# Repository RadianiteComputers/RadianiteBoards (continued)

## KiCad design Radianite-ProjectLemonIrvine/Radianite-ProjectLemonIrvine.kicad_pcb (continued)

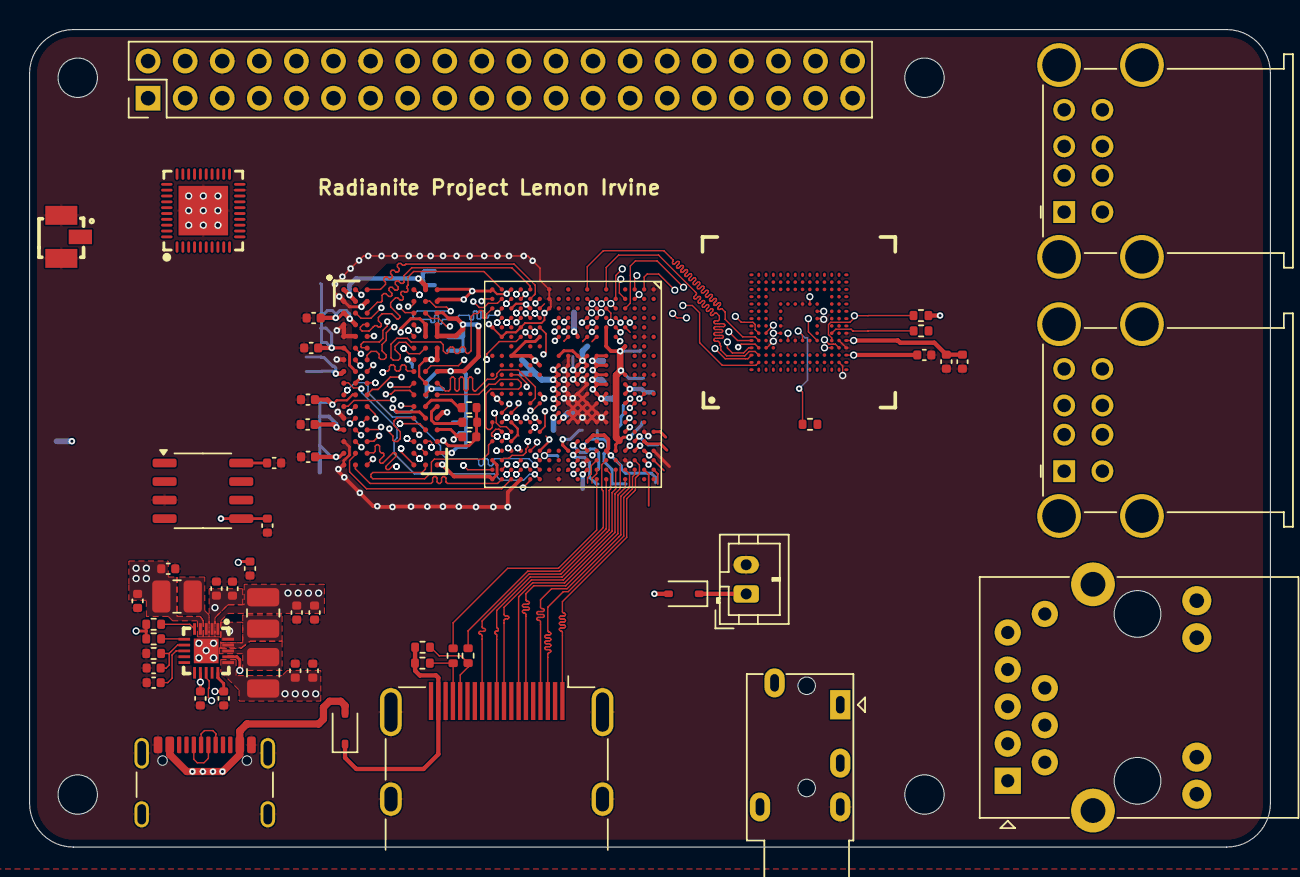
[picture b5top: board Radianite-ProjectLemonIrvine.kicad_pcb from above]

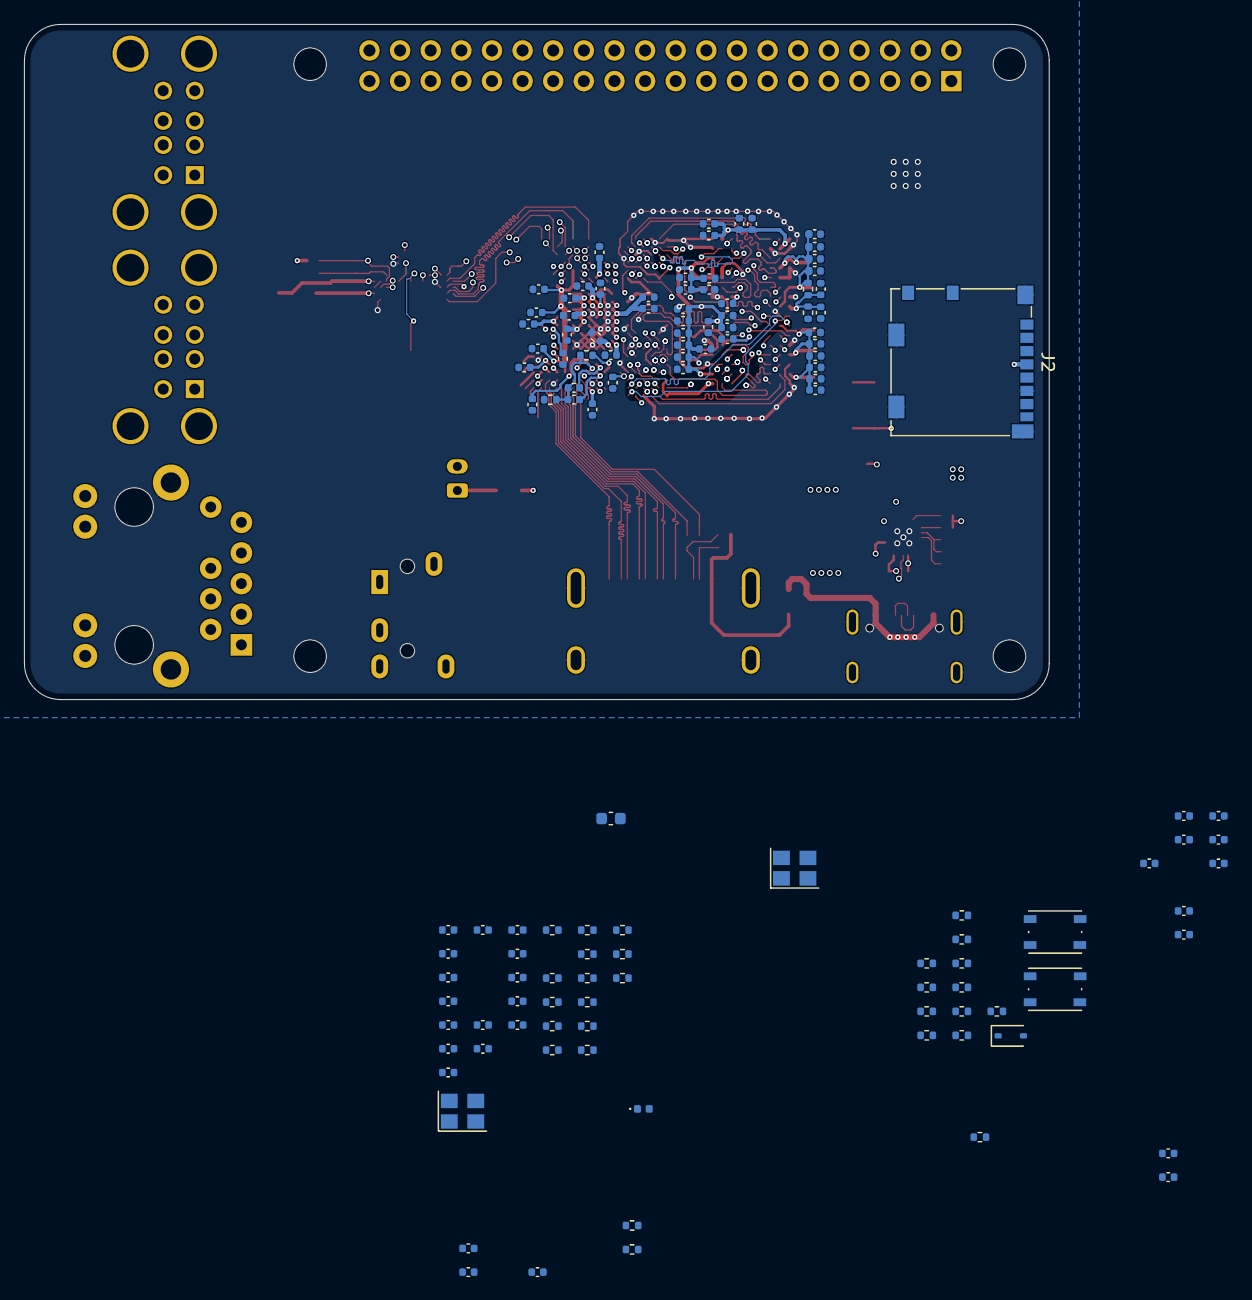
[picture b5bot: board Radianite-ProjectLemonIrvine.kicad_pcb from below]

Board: 6 copper layers, 85.0 x 56.0 mm, 181 parts (121 on the bottom side), 211 nets.

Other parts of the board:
C34#2, C35#2, C36#2, C55#2: 100n; C_0402_1005Metric

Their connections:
GND: C34#2.2, C35#2.2, C36#2.2, C55#2.2; also elsewhere on the board
VRAM: C34#2.1, C35#2.1, C36#2.1, C55#2.1; also elsewhere on the board

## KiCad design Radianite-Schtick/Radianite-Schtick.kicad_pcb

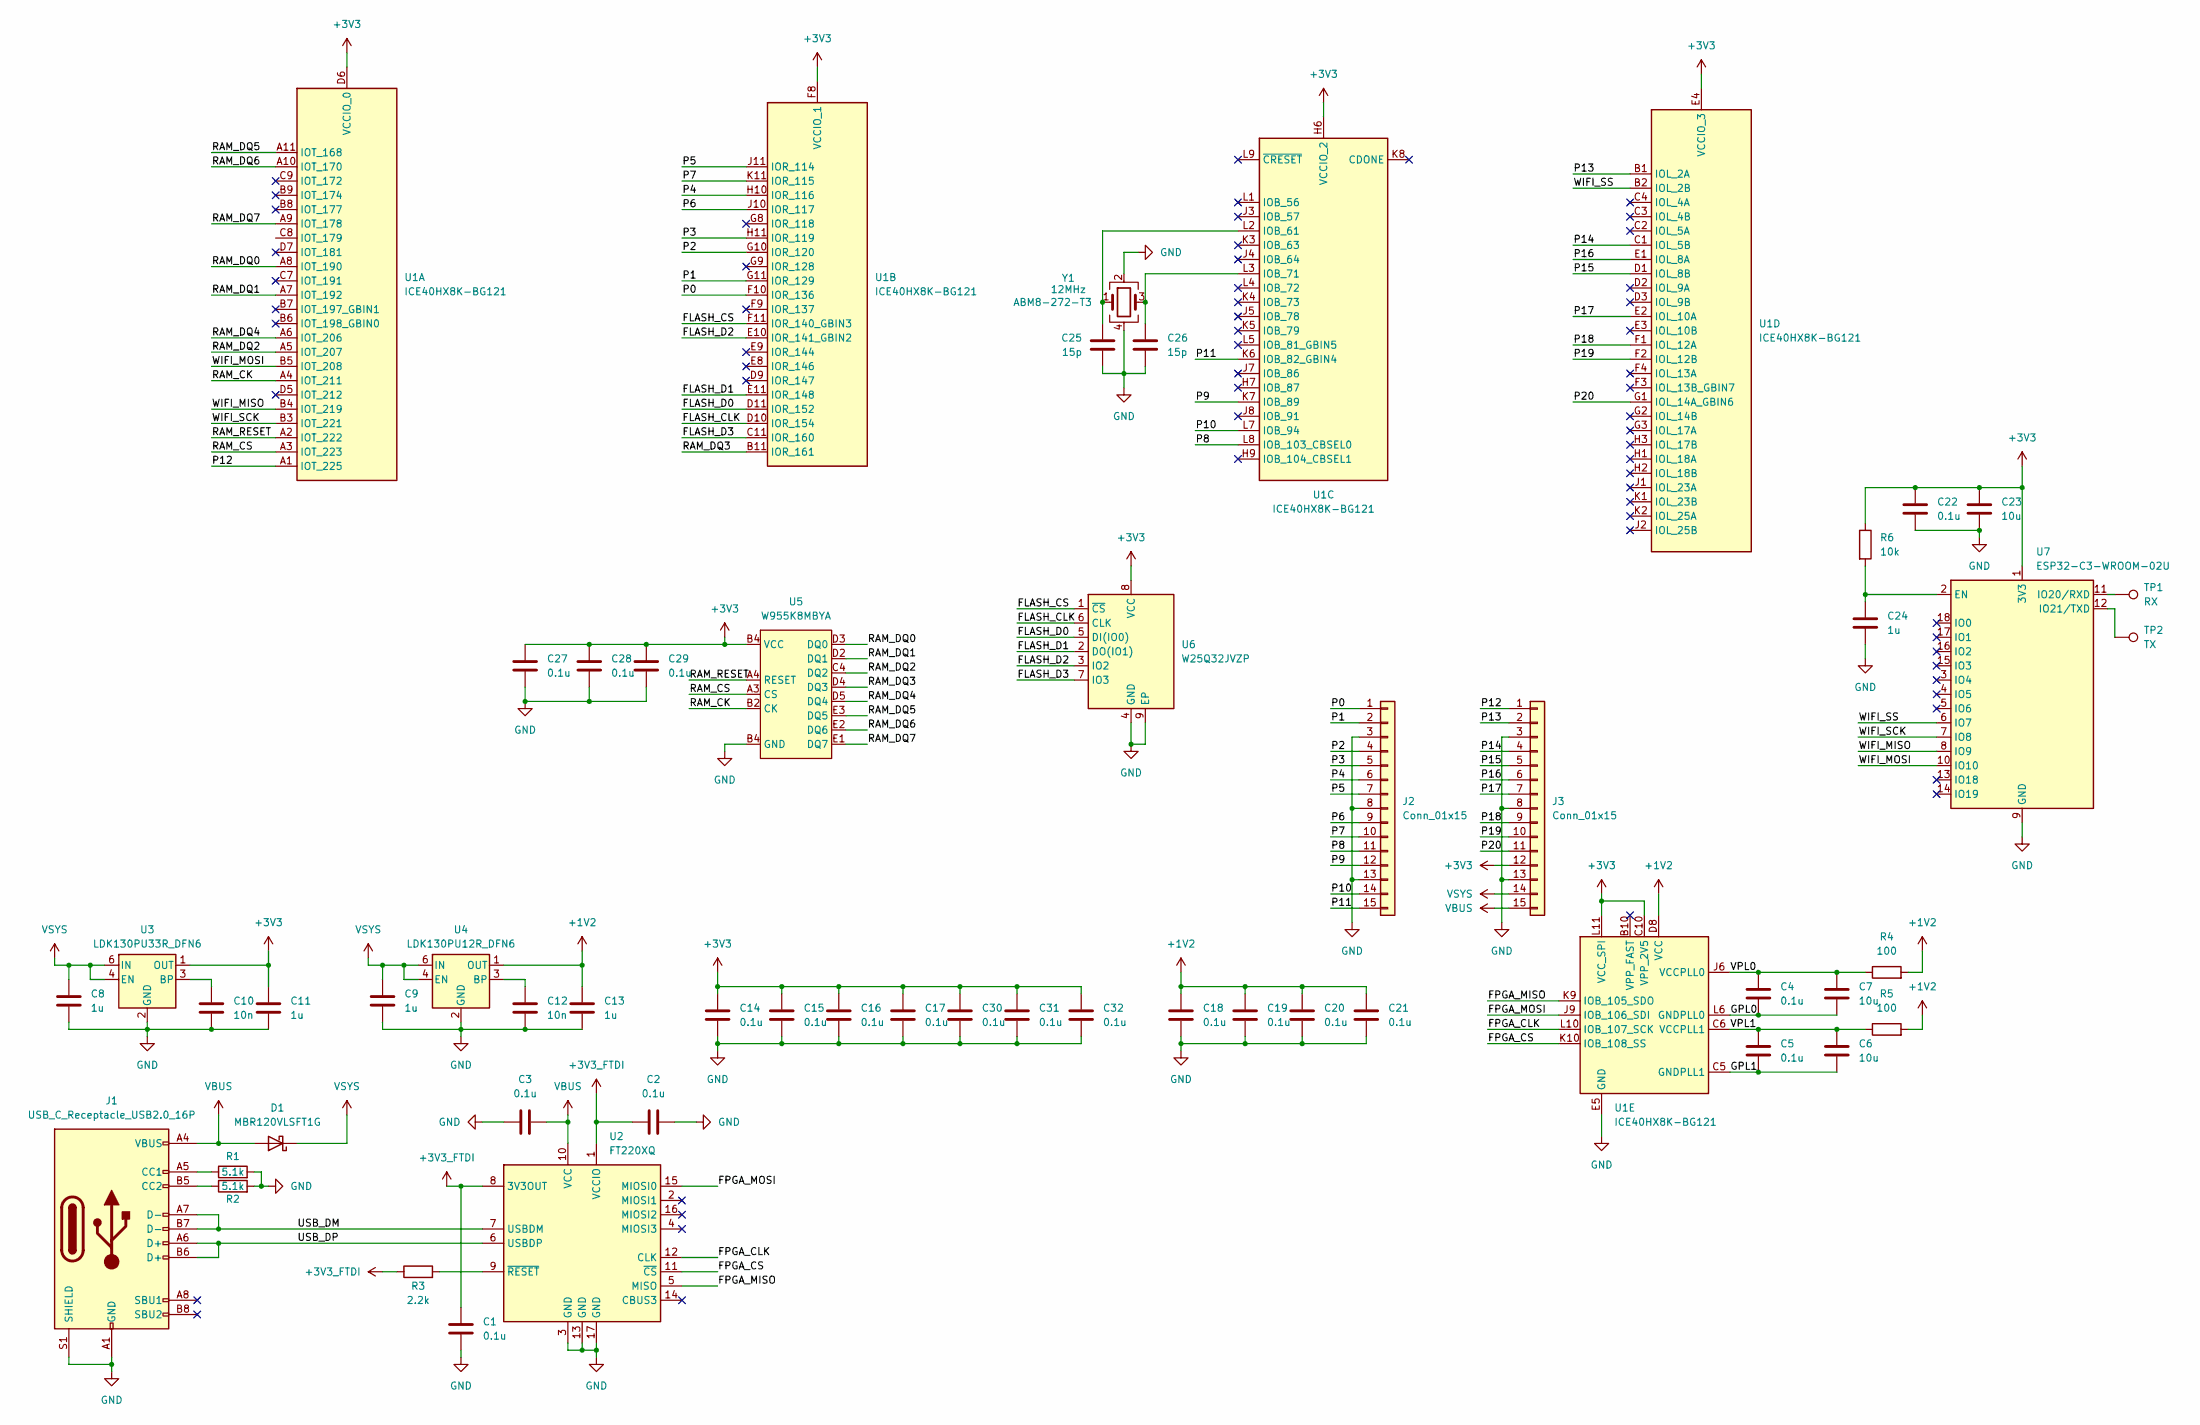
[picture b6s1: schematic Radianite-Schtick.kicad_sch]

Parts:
C1, C2, C3, C4, C5, C14, C15, C16, C17, C18, C19, C20, C21, C22, C27, C28, C29, C30, C31, C32: 0.1u; C_0402_1005Metric
C6, C7, C23: 10u; C_0402_1005Metric
C8, C9, C11, C13, C24: 1u; C_0402_1005Metric
C10, C12: 10n; C_0402_1005Metric
C25, C26: 15p; C_0402_1005Metric
D1: MBR120VLSFT1G; D_SOD-123F
J1: USB_C_Receptacle_USB2.0_16P; USB_C_Receptacle_GCT_USB4105-xx-A_16P_TopMnt_Horizontal
J2, J3: Conn_01x15; PinHeader_1x15_P2.54mm_Vertical
R1, R2: 5.1k; R_0402_1005Metric
R3: 2.2k; R_0402_1005Metric
R4, R5: 100; R_0402_1005Metric
R6: 10k; R_0402_1005Metric
TP1: RX; TestPoint_Pad_D1.0mm
TP2: TX; TestPoint_Pad_D1.0mm
U1: ICE40HX8K-BG121; BGA-121_9.0x9.0mm_Layout11x11_P0.8mm_Ball0.4mm_Pad0.35mm_NS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
U2: FT220XQ; QFN-16-1EP_4x4mm_P0.65mm_EP2.1x2.1mm
U3: LDK130PU33R_DFN6; DFN-6_1.3x1.2mm_P0.4mm
U4: LDK130PU12R_DFN6; DFN-6_1.3x1.2mm_P0.4mm
U5: W955K8MBYA
U6: W25Q32JVZP; Winbond_USON-8-1EP_3x2mm_P0.5mm_EP0.2x1.6mm
U7: ESP32-C3-WROOM-02U
Y1: 12MHz; Crystal_SMD_3225-4Pin_3.2x2.5mm

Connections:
+1V2: C13.1, C18.1, C19.1, C20.1, C21.1, R4.2, R5.2, U1.D4 (VCC), U1.D8 (VCC), U1.H4 (VCC), U1.H8 (VCC), U4.1 (OUT)
+3V3_FTDI: C1.1, C2.1, R3.1, U2.1 (VCCIO), U2.8 (3V3OUT)
/FLASH_CLK: U1.D10 (IOR_154), U6.6 (CLK)
/FLASH_CS: U1.F11 (IOR_140_GBIN3), U6.1 (~CS)
/FLASH_D0: U1.D11 (IOR_152), U6.5 (DI(IO0))
/FLASH_D1: U1.E11 (IOR_148), U6.2 (DO(IO1))
/FLASH_D2: U1.E10 (IOR_141_GBIN2), U6.3 (IO2)
/FLASH_D3: U1.C11 (IOR_160), U6.7 (IO3)
/FPGA_CLK: U1.L10 (IOB_107_SCK), U2.12 (CLK)
/FPGA_CS: U1.K10 (IOB_108_SS), U2.11 (~CS)
/FPGA_MISO: U1.K9 (IOB_105_SDO), U2.5 (MISO)
/FPGA_MOSI: U1.J9 (IOB_106_SDI), U2.15 (MIOSI0)
/GPL0: C4.2, C7.2, U1.L6 (GNDPLL0)
/GPL1: C5.2, C6.2, U1.C5 (GNDPLL1)
/P0: J2.1, U1.F10 (IOR_136)
/P1: J2.2, U1.G11 (IOR_129)
/P2: J2.4, U1.G10 (IOR_120)
/P3: J2.5, U1.H11 (IOR_119)
/P4: J2.6, U1.H10 (IOR_116)
/P5: J2.7, U1.J11 (IOR_114)
/P6: J2.9, U1.J10 (IOR_117)
/P7: J2.10, U1.K11 (IOR_115)
/P8: J2.11, U1.L8 (IOB_103_CBSEL0)
/P9: J2.12, U1.K7 (IOB_89)
/P10: J2.14, U1.L7 (IOB_94)
/P11: J2.15, U1.K6 (IOB_82_GBIN4)
/P12: J3.1, U1.A1 (IOT_225)
/P13: J3.2, U1.B1 (IOL_2A)
/P14: J3.4, U1.C1 (IOL_5B)
/P15: J3.5, U1.D1 (IOL_8B)
/P16: J3.6, U1.E1 (IOL_8A)
/P17: J3.7, U1.E2 (IOL_10A)
/P18: J3.9, U1.F1 (IOL_12A)
/P19: J3.10, U1.F2 (IOL_12B)
/P20: J3.11, U1.G1 (IOL_14A_GBIN6)
/RAM_CK: U1.A4 (IOT_211), U5.B2 (CK)
/RAM_CS: U1.A3 (IOT_223), U5.A3 (CS)
/RAM_DQ0: U1.A8 (IOT_190), U5.D3 (DQ0)
/RAM_DQ1: U1.A7 (IOT_192), U5.D2 (DQ1)
/RAM_DQ2: U1.A5 (IOT_207), U5.C4 (DQ2)
/RAM_DQ3: U1.B11 (IOR_161), U5.D4 (DQ3)
/RAM_DQ4: U1.A6 (IOT_206), U5.D5 (DQ4)
/RAM_DQ5: U1.A11 (IOT_168), U5.E3 (DQ5)
/RAM_DQ6: U1.A10 (IOT_170), U5.E2 (DQ6)
/RAM_DQ7: U1.A9 (IOT_178), U5.E1 (DQ7)
/RAM_RESET: U1.A2 (IOT_222), U5.A4 (RESET)
/USB_DM: J1.A7 (D-), J1.B7 (D-), U2.7 (USBDM)
/USB_DP: J1.A6 (D+), J1.B6 (D+), U2.6 (USBDP)
/VPL0: C4.1, C7.1, R4.1, U1.J6 (VCCPLL0)
/VPL1: C5.1, C6.1, R5.1, U1.C6 (VCCPLL1)
/WIFI_MISO: U1.B4 (IOT_219), U7.8 (IO9)
/WIFI_MOSI: U1.B5 (IOT_208), U7.10 (IO10)
/WIFI_SCK: U1.B3 (IOT_221), U7.7 (IO8)
/WIFI_SS: U1.B2 (IOL_2B), U7.6 (IO7)
unnamed: J1.A5 (CC1), R1.1
unnamed: J1.B5 (CC2), R2.1
unnamed: C25.1, U1.L2 (IOB_61), Y1.1
unnamed: C26.1, U1.L3 (IOB_71), Y1.3
unnamed: R3.2, U2.9 (~RESET)
unnamed: C10.1, U3.3 (BP)
unnamed: C12.1, U4.3 (BP)
unnamed: C24.1, R6.2, U7.2 (EN)
unnamed: TP1.1, U7.11 (IO20/RXD)
unnamed: TP2.1, U7.12 (IO21/TXD)
VBUS: C3.2, D1.2 (A), J1.A4 (VBUS), J1.A9 (VBUS), J1.B4 (VBUS), J1.B9 (VBUS), J3.15, U2.10 (VCC)
VSYS: C8.1, C9.1, D1.1 (K), J3.14, U3.4 (EN), U3.6 (IN), U4.4 (EN), U4.6 (IN)

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
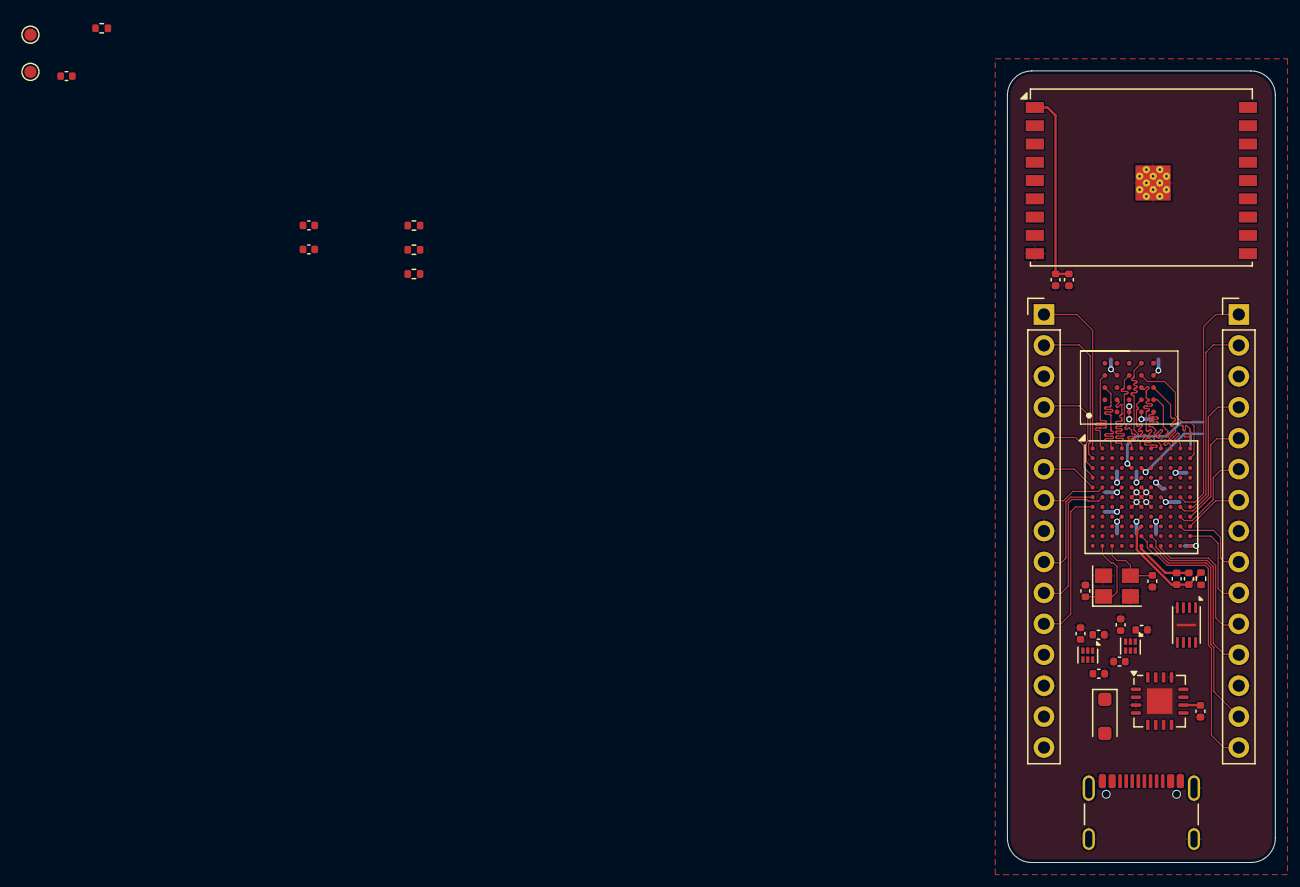
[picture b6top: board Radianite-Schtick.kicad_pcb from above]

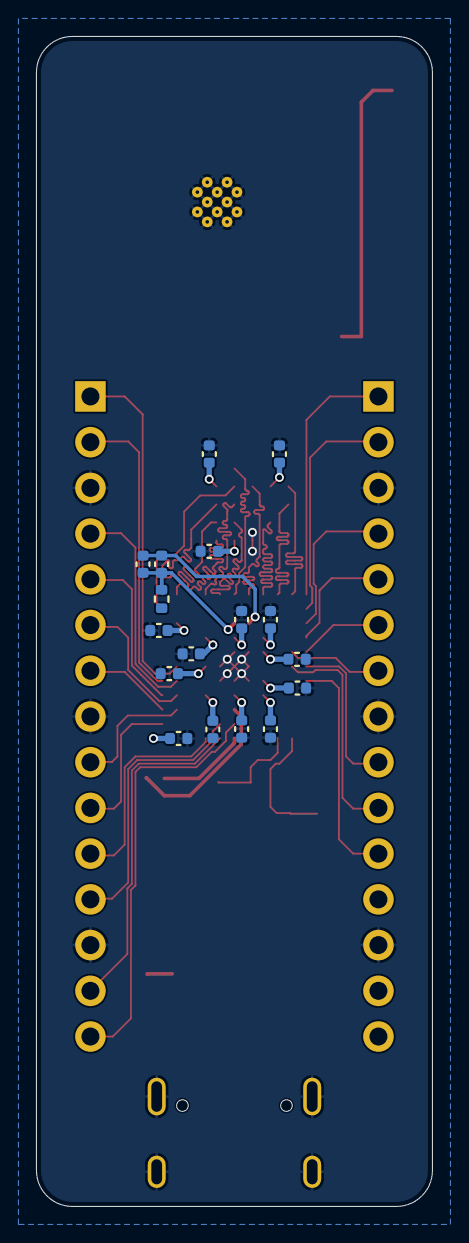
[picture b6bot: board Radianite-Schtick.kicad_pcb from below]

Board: 4 copper layers, 22.0 x 65.0 mm, 52 parts (17 on the bottom side), 68 nets.

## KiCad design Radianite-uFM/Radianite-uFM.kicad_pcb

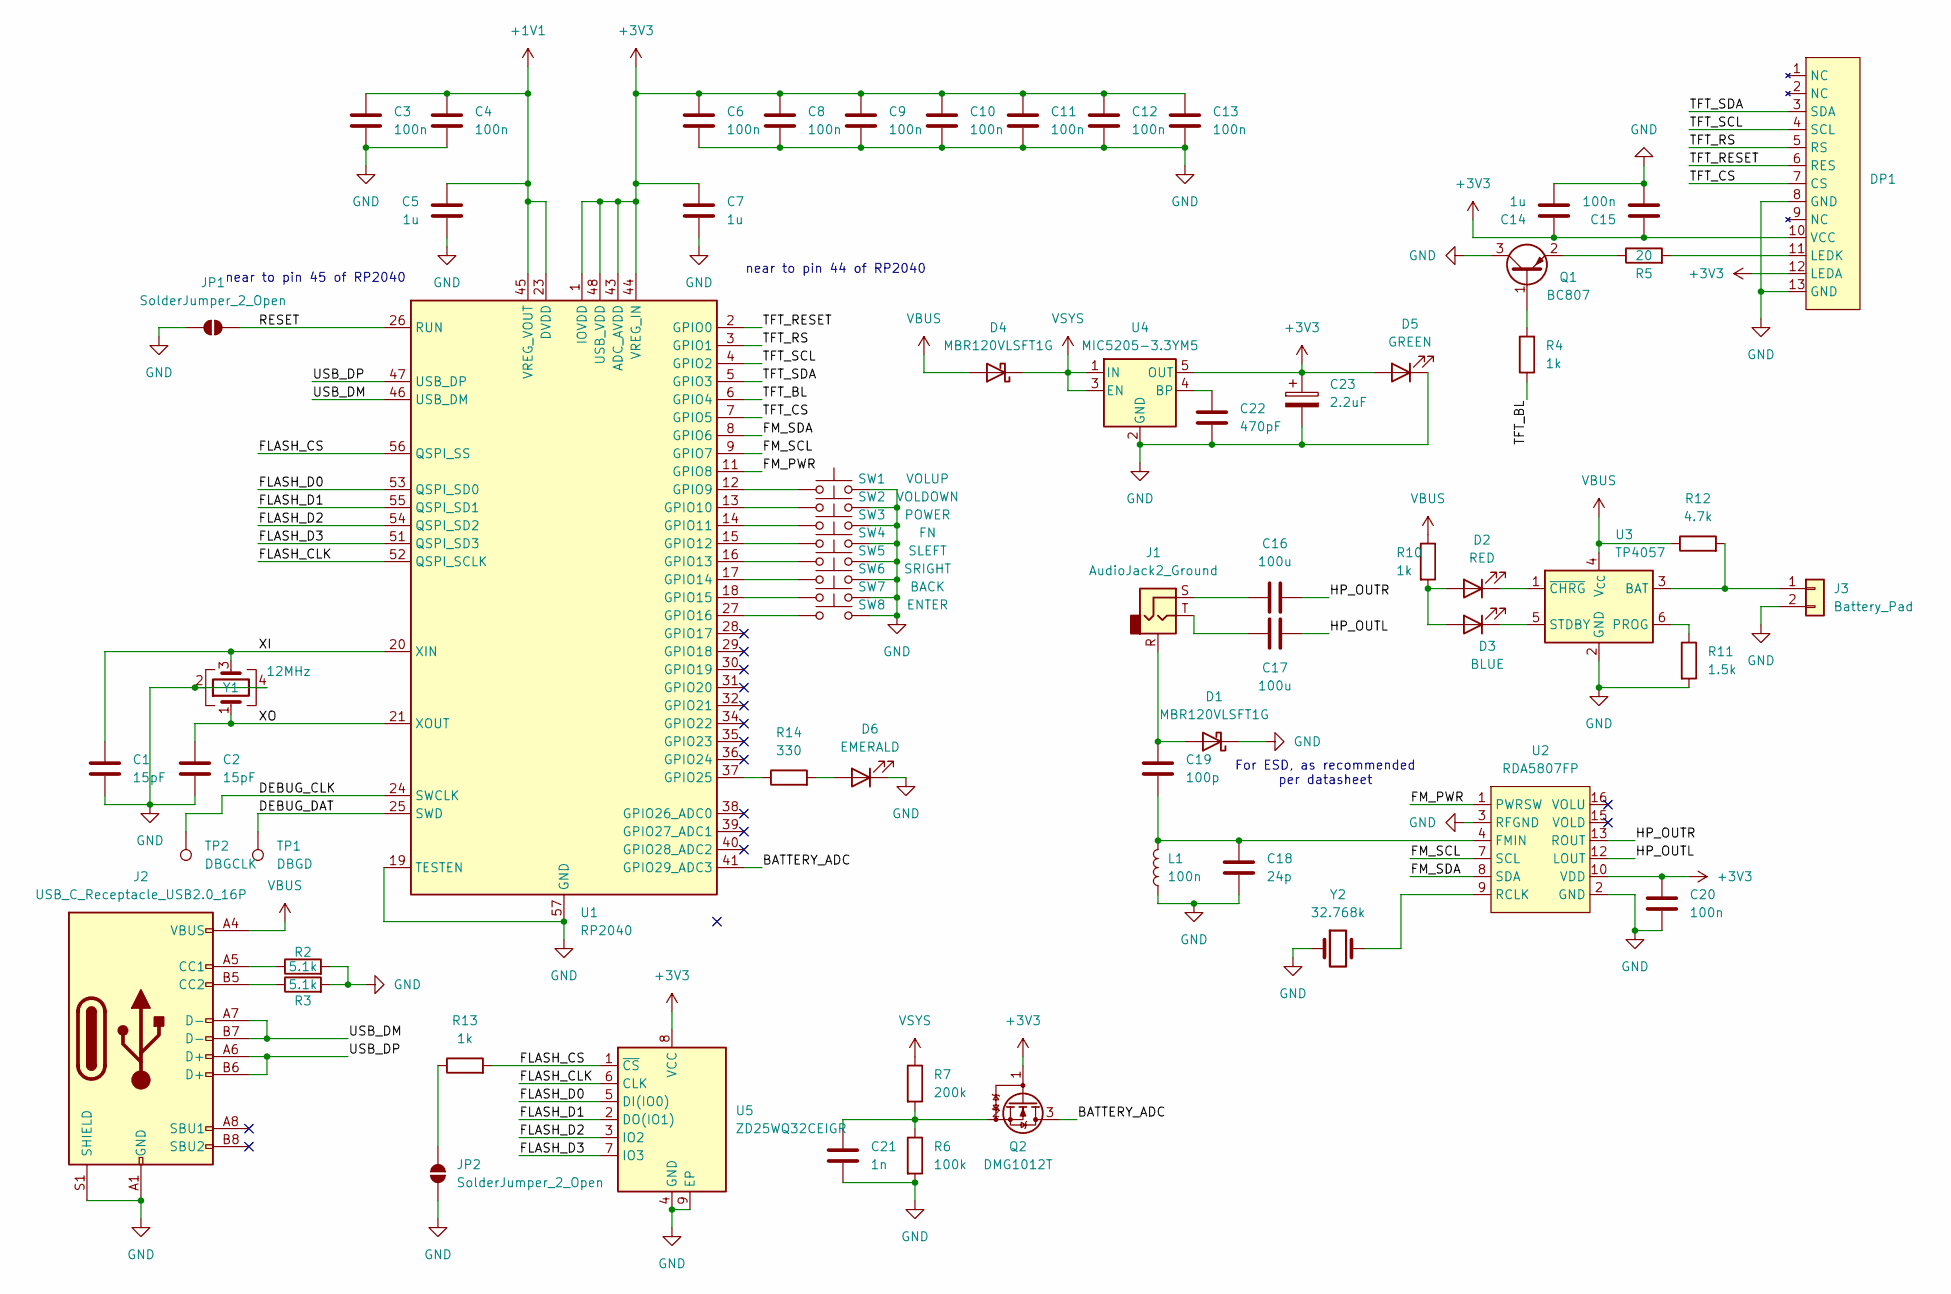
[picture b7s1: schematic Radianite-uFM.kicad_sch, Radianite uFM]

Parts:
C1, C2: 15pF; C_0402_1005Metric
C3, C4, C6, C8, C9, C10, C11, C12, C13, C15: 100n; C_0402_1005Metric
C5, C7, C14: 1u; C_0402_1005Metric
C16, C17: 100u; C_0603_1608Metric
C18: 24p; C_0603_1608Metric
C19: 100p; C_0603_1608Metric
C20: 100n; C_0603_1608Metric
C21: 1n; C_0402_1005Metric
C22: 470pF; C_0402_1005Metric
C23: 2.2uF; CP_EIA-1608-08_AVX-J
D1, D4: MBR120VLSFT1G; D_SOD-123F
D2: RED; LED_0402_1005Metric
D3: BLUE; LED_0402_1005Metric
D5: GREEN; LED_0402_1005Metric
D6: EMERALD; LED_0402_1005Metric
DP1: N114-2413THBIG01-H13
J1: AudioJack2_Ground; Jack_3.5mm_Lumberg_1503_07_Horizontal
J2: USB_C_Receptacle_USB2.0_16P; USB_C_Receptacle_GCT_USB4105-xx-A_16P_TopMnt_Horizontal
J3: Battery_Pad; SolderWire-0.1sqmm_1x02_P3.6mm_D0.4mm_OD1mm
JP1, JP2: SolderJumper_2_Open; SolderJumper-2_P1.3mm_Open_Pad1.0x1.5mm
L1: 100n; L_0603_1608Metric
Q1: BC807; SOT-23
Q2: DMG1012T; SOT-523
R2, R3: 5.1k; R_0402_1005Metric
R4, R10, R13: 1k; R_0402_1005Metric
R5: 20; R_0402_1005Metric
R6: 100k; R_0402_1005Metric
R7: 200k; R_0402_1005Metric
R11: 1.5k; R_0402_1005Metric
R12: 4.7k; R_0402_1005Metric
R14: 330; R_0402_1005Metric
SW1: VOLUP; SW_Push_1P1T-MP_NO_Horizontal_Alps_SKRTLAE010
SW2: VOLDOWN; SW_Push_1P1T-MP_NO_Horizontal_Alps_SKRTLAE010
SW3: POWER; SW_Push_1P1T-MP_NO_Horizontal_Alps_SKRTLAE010
SW4: FN; SW_Push_1P1T-MP_NO_Horizontal_Alps_SKRTLAE010
SW5: SLEFT; SW_Push_1P1T_NO_Vertical_Wuerth_434133025816
SW6: SRIGHT; SW_Push_1P1T_NO_Vertical_Wuerth_434133025816
SW7: BACK; SW_Push_1P1T_NO_Vertical_Wuerth_434133025816
SW8: ENTER; SW_Push_1P1T_NO_Vertical_Wuerth_434133025816
TP1: DBGD; TestPoint_Pad_D1.0mm
TP2: DBGCLK; TestPoint_Pad_D1.0mm
U1: RP2040; QFN-56-1EP_7x7mm_P0.4mm_EP3.2x3.2mm
U2: RDA5807FP; SOP-16_3.9x9.9mm_P1.27mm
U3: TP4057; TSOT-23-6
U4: MIC5205-3.3YM5; SOT-23-5
U5: ZD25WQ32CEIGR; Winbond_USON-8-1EP_3x2mm_P0.5mm_EP0.2x1.6mm
Y1: 12MHz; Crystal_SMD_2520-4Pin_2.5x2.0mm
Y2: 32.768k; Crystal_SMD_0603-2Pin_6.0x3.5mm

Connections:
+1V1: C3.1, C4.1, C5.1, U1.23 (DVDD), U1.45 (VREG_VOUT), U1.50 (DVDD)
+3V3: C6.1, C7.1, C8.1, C9.1, C10.1, C11.1, C12.1, C13.1, C14.1, C15.1, C20.1, C23.1, D5.2 (A), DP1.10 (VCC), DP1.12 (LEDA), Q2.1 (G), U1.1 (IOVDD), U1.10 (IOVDD), U1.22 (IOVDD), U1.33 (IOVDD), U1.42 (IOVDD), U1.43 (ADC_AVDD), U1.44 (VREG_IN), U1.48 (USB_VDD), U1.49 (IOVDD), U2.10 (VDD), U4.5 (OUT), U5.8 (VCC)
/BATTERY_ADC: Q2.3 (D), U1.41 (GPIO29_ADC3)
/DEBUG_CLK: TP2.1, U1.24 (SWCLK)
/DEBUG_DAT: TP1.1, U1.25 (SWD)
/FLASH_CLK: U1.52 (QSPI_SCLK), U5.6 (CLK)
/FLASH_CS: R13.2, U1.56 (QSPI_SS), U5.1 (~CS)
/FLASH_D0: U1.53 (QSPI_SD0), U5.5 (DI(IO0))
/FLASH_D1: U1.55 (QSPI_SD1), U5.2 (DO(IO1))
/FLASH_D2: U1.54 (QSPI_SD2), U5.3 (IO2)
/FLASH_D3: U1.51 (QSPI_SD3), U5.7 (IO3)
/FM_PWR: U1.11 (GPIO8), U2.1 (PWRSW)
/FM_SCL: U1.9 (GPIO7), U2.7 (SCL)
/FM_SDA: U1.8 (GPIO6), U2.8 (SDA)
/HP_OUTL: C17.2, U2.12 (LOUT)
/HP_OUTR: C16.2, U2.13 (ROUT)
/RESET: JP1.2 (B), U1.26 (RUN)
/TFT_BL: R4.1, U1.6 (GPIO4)
/TFT_CS: DP1.7 (CS), U1.7 (GPIO5)
/TFT_RESET: DP1.6 (RES), U1.2 (GPIO0)
/TFT_RS: DP1.5 (RS), U1.3 (GPIO1)
/TFT_SCL: DP1.4 (SCL), U1.4 (GPIO2)
/TFT_SDA: DP1.3 (SDA), U1.5 (GPIO3)
/USB_DM: J2.A7 (D-), J2.B7 (D-), U1.46 (USB_DM)
/USB_DP: J2.A6 (D+), J2.B6 (D+), U1.47 (USB_DP)
/XI: C1.1, U1.20 (XIN), Y1.3
/XO: C2.1, U1.21 (XOUT), Y1.1
GND: C1.2, C2.2, C3.2, C4.2, C5.2, C6.2, C7.2, C8.2, C9.2, C10.2, C11.2, C12.2, C13.2, C14.2, C15.2, C18.2, C20.2, C21.2, C22.2, C23.2, D1.1 (K), D5.1 (K), D6.1 (K), DP1.8 (GND), DP1.13 (GND), J2.A1 (GND), J2.A12 (GND), J2.B1 (GND), J2.B12 (GND), J2.S1 (SHIELD), J3.2, JP1.1 (A), JP2.2 (B), L1.1, Q1.3 (C), R2.2, R3.2, R6.2, R11.2, SW1.2, SW2.2, SW3.2, SW4.2, SW5.2, SW6.2, SW7.2, SW8.2, U1.19 (TESTEN), U1.57 (GND), U2.2 (GND), U2.3 (RFGND), U2.5 (GND), U2.6 (GND), U2.11 (GND), U2.14 (GND), U3.2 (GND), U4.2 (GND), U5.4 (GND), U5.9 (EP), Y1.2, Y1.4, Y2.1
unnamed: C16.1, J1.S
unnamed: C17.1, J1.T
unnamed: C19.1, D1.2 (A), J1.R
unnamed: D2.2 (A), D3.2 (A), R10.2
unnamed: D2.1 (K), U3.1 (~CHRG)
unnamed: D3.1 (K), U3.5 (STDBY)
unnamed: D6.2 (A), R14.2
unnamed: DP1.11 (LEDK), R5.2
unnamed: J2.A5 (CC1), R2.1
unnamed: J2.B5 (CC2), R3.1
unnamed: J3.1, R12.2, U3.3 (BAT)
unnamed: JP2.1 (A), R13.1
unnamed: Q1.1 (B), R4.2
unnamed: Q1.2 (E), R5.1
unnamed: C21.1, Q2.2 (S), R6.1, R7.2
unnamed: SW1.1, U1.12 (GPIO9)
unnamed: SW2.1, U1.13 (GPIO10)
unnamed: SW3.1, U1.14 (GPIO11)
unnamed: SW4.1, U1.15 (GPIO12)
unnamed: SW5.1, U1.16 (GPIO13)
unnamed: SW6.1, U1.17 (GPIO14)
unnamed: SW7.1, U1.18 (GPIO15)
unnamed: SW8.1, U1.27 (GPIO16)
unnamed: R14.1, U1.37 (GPIO25)
unnamed: C18.1, C19.2, L1.2, U2.4 (FMIN)
unnamed: U2.9 (RCLK), Y2.2
unnamed: R11.1, U3.6 (PROG)
unnamed: C22.1, U4.4 (BP)
VBUS: D4.2 (A), J2.A4 (VBUS), J2.A9 (VBUS), J2.B4 (VBUS), J2.B9 (VBUS), R10.1, R12.1, U3.4 (V_{CC})
VSYS: D4.1 (K), R7.1, U4.1 (IN), U4.3 (EN)

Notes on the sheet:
near to pin 45 of RP2040
For ESD, as recommended per datasheet
near to pin 44 of RP2040

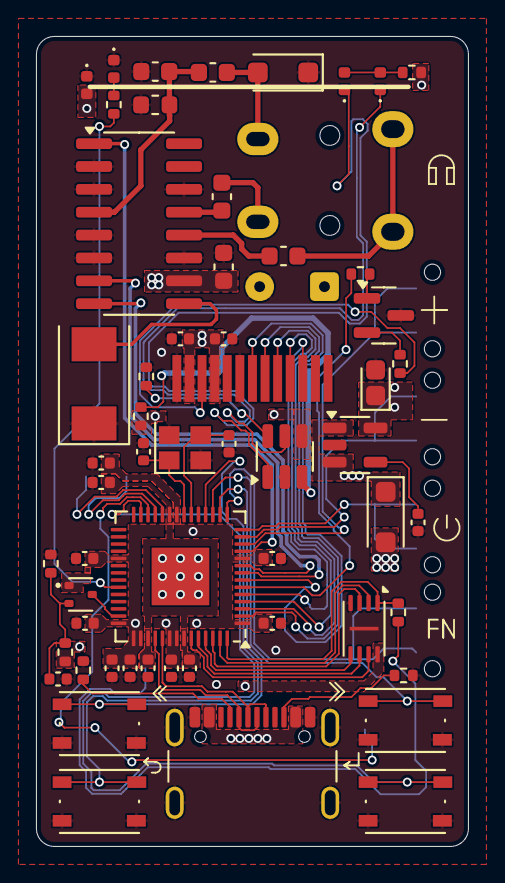
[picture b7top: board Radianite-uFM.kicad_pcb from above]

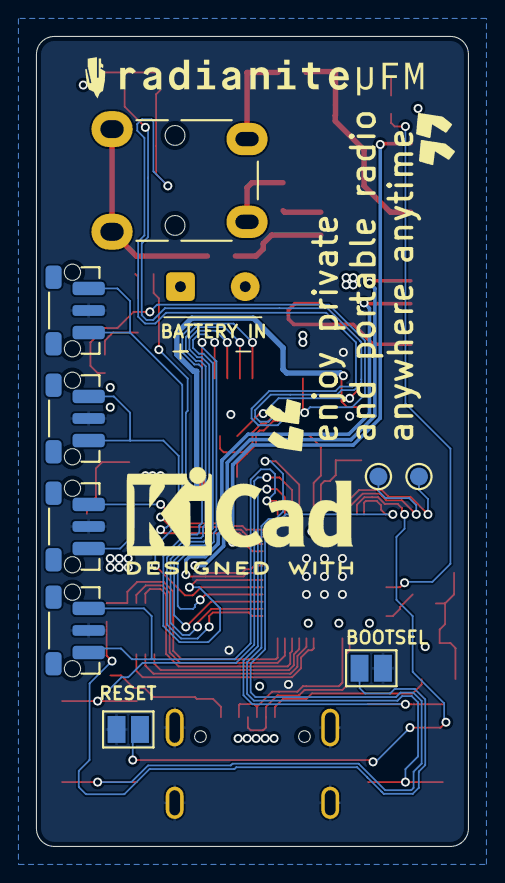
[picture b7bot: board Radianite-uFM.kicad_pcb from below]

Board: 4 copper layers, 24.0 x 45.0 mm, 66 parts (10 on the bottom side), 58 nets.
